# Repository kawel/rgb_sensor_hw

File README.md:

# rgb_sensor_hw
RGB sensor Kicad project

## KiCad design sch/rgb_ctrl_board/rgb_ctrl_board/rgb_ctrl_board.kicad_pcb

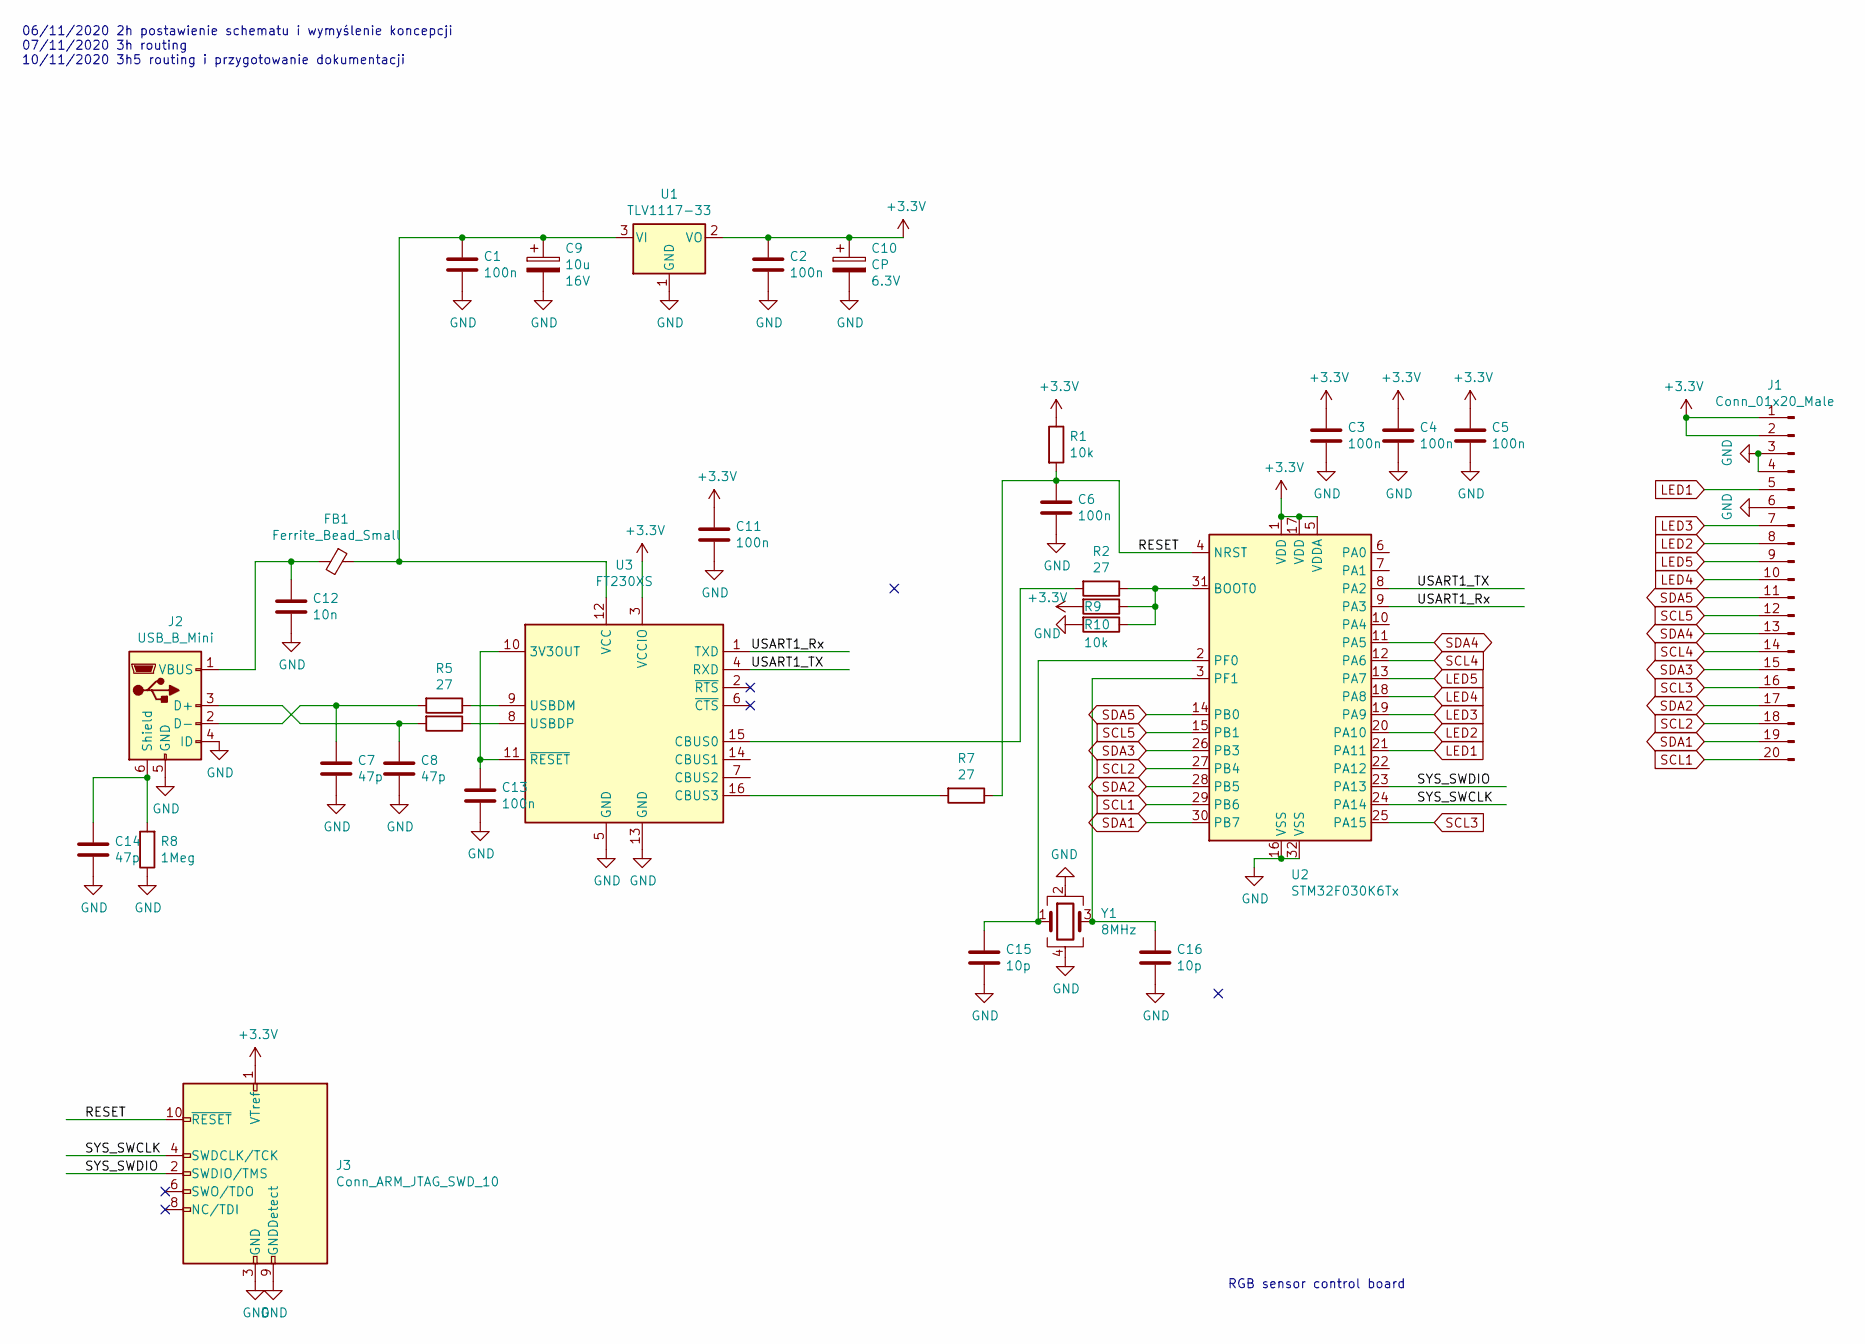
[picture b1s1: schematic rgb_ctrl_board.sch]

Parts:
C1, C2, C3, C4, C5, C6, C11, C13: 100n; C_0603_1608Metric_Pad1.08x0.95mm_HandSolder
C7, C8, C14: 47p; C_0603_1608Metric_Pad1.08x0.95mm_HandSolder
C9: 10u; C_Elec_4x5.4; Voltage 16V
C10: CP; C_Elec_5x5.4; Voltage 6.3V
C12: 10n; C_0603_1608Metric_Pad1.08x0.95mm_HandSolder
C15, C16: 10p; C_0603_1608Metric_Pad1.08x0.95mm_HandSolder
FB1: Ferrite_Bead_Small; L_0603_1608Metric_Pad1.05x0.95mm_HandSolder
J1: Conn_01x20_Male; JST_PHD_S20B-PHDSS_2x10_P2.00mm_Horizontal
J2: USB_B_Mini; USB_Micro-B_Molex_47346-0001
J3: Conn_ARM_JTAG_SWD_10; PinHeader_2x05_P1.27mm_Vertical
R1, R9, R10: 10k; R_0603_1608Metric_Pad0.98x0.95mm_HandSolder
R2, R5, R6, R7: 27; R_0603_1608Metric_Pad0.98x0.95mm_HandSolder
R8: 1Meg; R_0603_1608Metric_Pad0.98x0.95mm_HandSolder
U1: TLV1117-33; SOT-223-3_TabPin2
U2: STM32F030K6Tx; LQFP-32_7x7mm_P0.8mm
U3: FT230XS; SSOP-16_3.9x4.9mm_P0.635mm
Y1: 8MHz; Oscillator_SMD_TXC_7C-4Pin_5.0x3.2mm_HandSoldering

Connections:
+3V3: C2.1, C3.1, C4.1, C5.1, C10.1, C11.1, J1.1, J1.2, J3.1 (VTref), R1.1, R9.2, U1.2 (VO), U2.1 (VDD), U2.5 (VDDA), U2.17 (VDD), U3.3 (VCCIO)
/RESET: C6.1, J3.10 (~RESET~), R1.2, R7.1, U2.4 (NRST)
/SYS_SWCLK: J3.4 (SWDCLK/TCK), U2.24 (PA14)
/SYS_SWDIO: J3.2 (SWDIO/TMS), U2.23 (PA13)
/USART1_Rx: U2.9 (PA3), U3.1 (TXD)
/USART1_TX: U2.8 (PA2), U3.4 (RXD)
GND: C1.2, C2.2, C3.2, C4.2, C5.2, C6.2, C7.2, C8.2, C9.2, C10.2, C11.2, C12.2, C13.2, C14.2, C15.2, C16.2, J1.3, J1.4, J1.6, J2.4 (ID), J2.5 (GND), J3.3 (GND), J3.5 (GND), J3.9 (GNDDetect), R8.1, R10.2, U1.1 (GND), U2.16 (VSS), U2.32 (VSS), U3.5 (GND), U3.13 (GND), Y1.2, Y1.4
LED1: J1.5, U2.21 (PA11)
LED2: J1.8, U2.20 (PA10)
LED3: J1.7, U2.19 (PA9)
LED4: J1.10, U2.18 (PA8)
LED5: J1.9, U2.13 (PA7)
unnamed: C1.1, C9.1, FB1.1, U1.3 (VI), U3.12 (VCC)
unnamed: C7.1, J2.2 (D-), R5.2
unnamed: C8.1, J2.3 (D+), R6.2
unnamed: C12.1, FB1.2, J2.1 (VBUS)
unnamed: C13.1, U3.10 (3V3OUT), U3.11 (~RESET)
unnamed: C14.1, J2.6 (Shield), R8.2
unnamed: C15.1, U2.2 (PF0), Y1.1
unnamed: C16.1, U2.3 (PF1), Y1.3
unnamed: R2.2, U3.15 (CBUS0)
unnamed: R5.1, U3.9 (USBDM)
unnamed: R6.1, U3.8 (USBDP)
unnamed: R7.2, U3.16 (CBUS3)
unnamed: R2.1, R9.1, R10.1, U2.31 (BOOT0)
SCL1: J1.20, U2.29 (PB6)
SCL2: J1.18, U2.27 (PB4)
SCL3: J1.16, U2.25 (PA15)
SCL4: J1.14, U2.12 (PA6)
SCL5: J1.12, U2.15 (PB1)
SDA1: J1.19, U2.30 (PB7)
SDA2: J1.17, U2.28 (PB5)
SDA3: J1.15, U2.26 (PB3)
SDA4: J1.13, U2.11 (PA5)
SDA5: J1.11, U2.14 (PB0)

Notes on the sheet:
06/11/2020 2h postawienie schematu i wymyślenie koncepcji 07/11/2020 3h routing 10/11/2020 3h5 routing i przygotowanie dokumentacji
RGB sensor control board

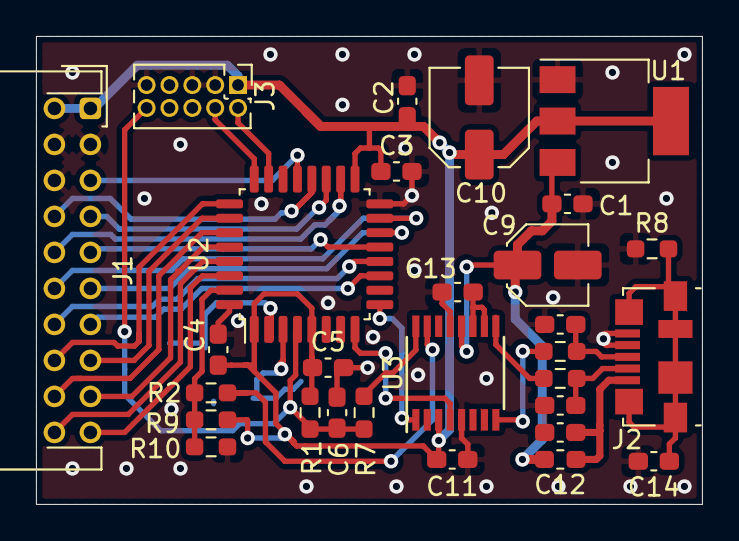
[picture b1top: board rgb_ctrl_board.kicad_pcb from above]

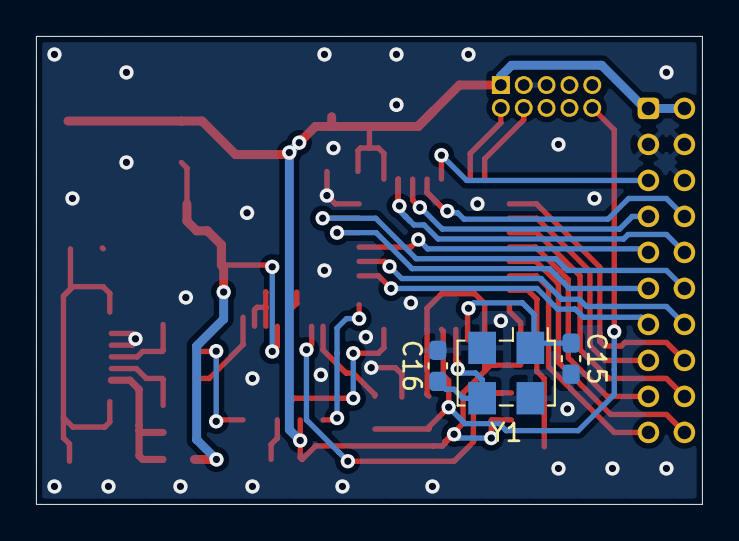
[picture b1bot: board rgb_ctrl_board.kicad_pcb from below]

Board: 2 copper layers, 37.0 x 26.0 mm, 32 parts (3 on the bottom side), 35 nets.

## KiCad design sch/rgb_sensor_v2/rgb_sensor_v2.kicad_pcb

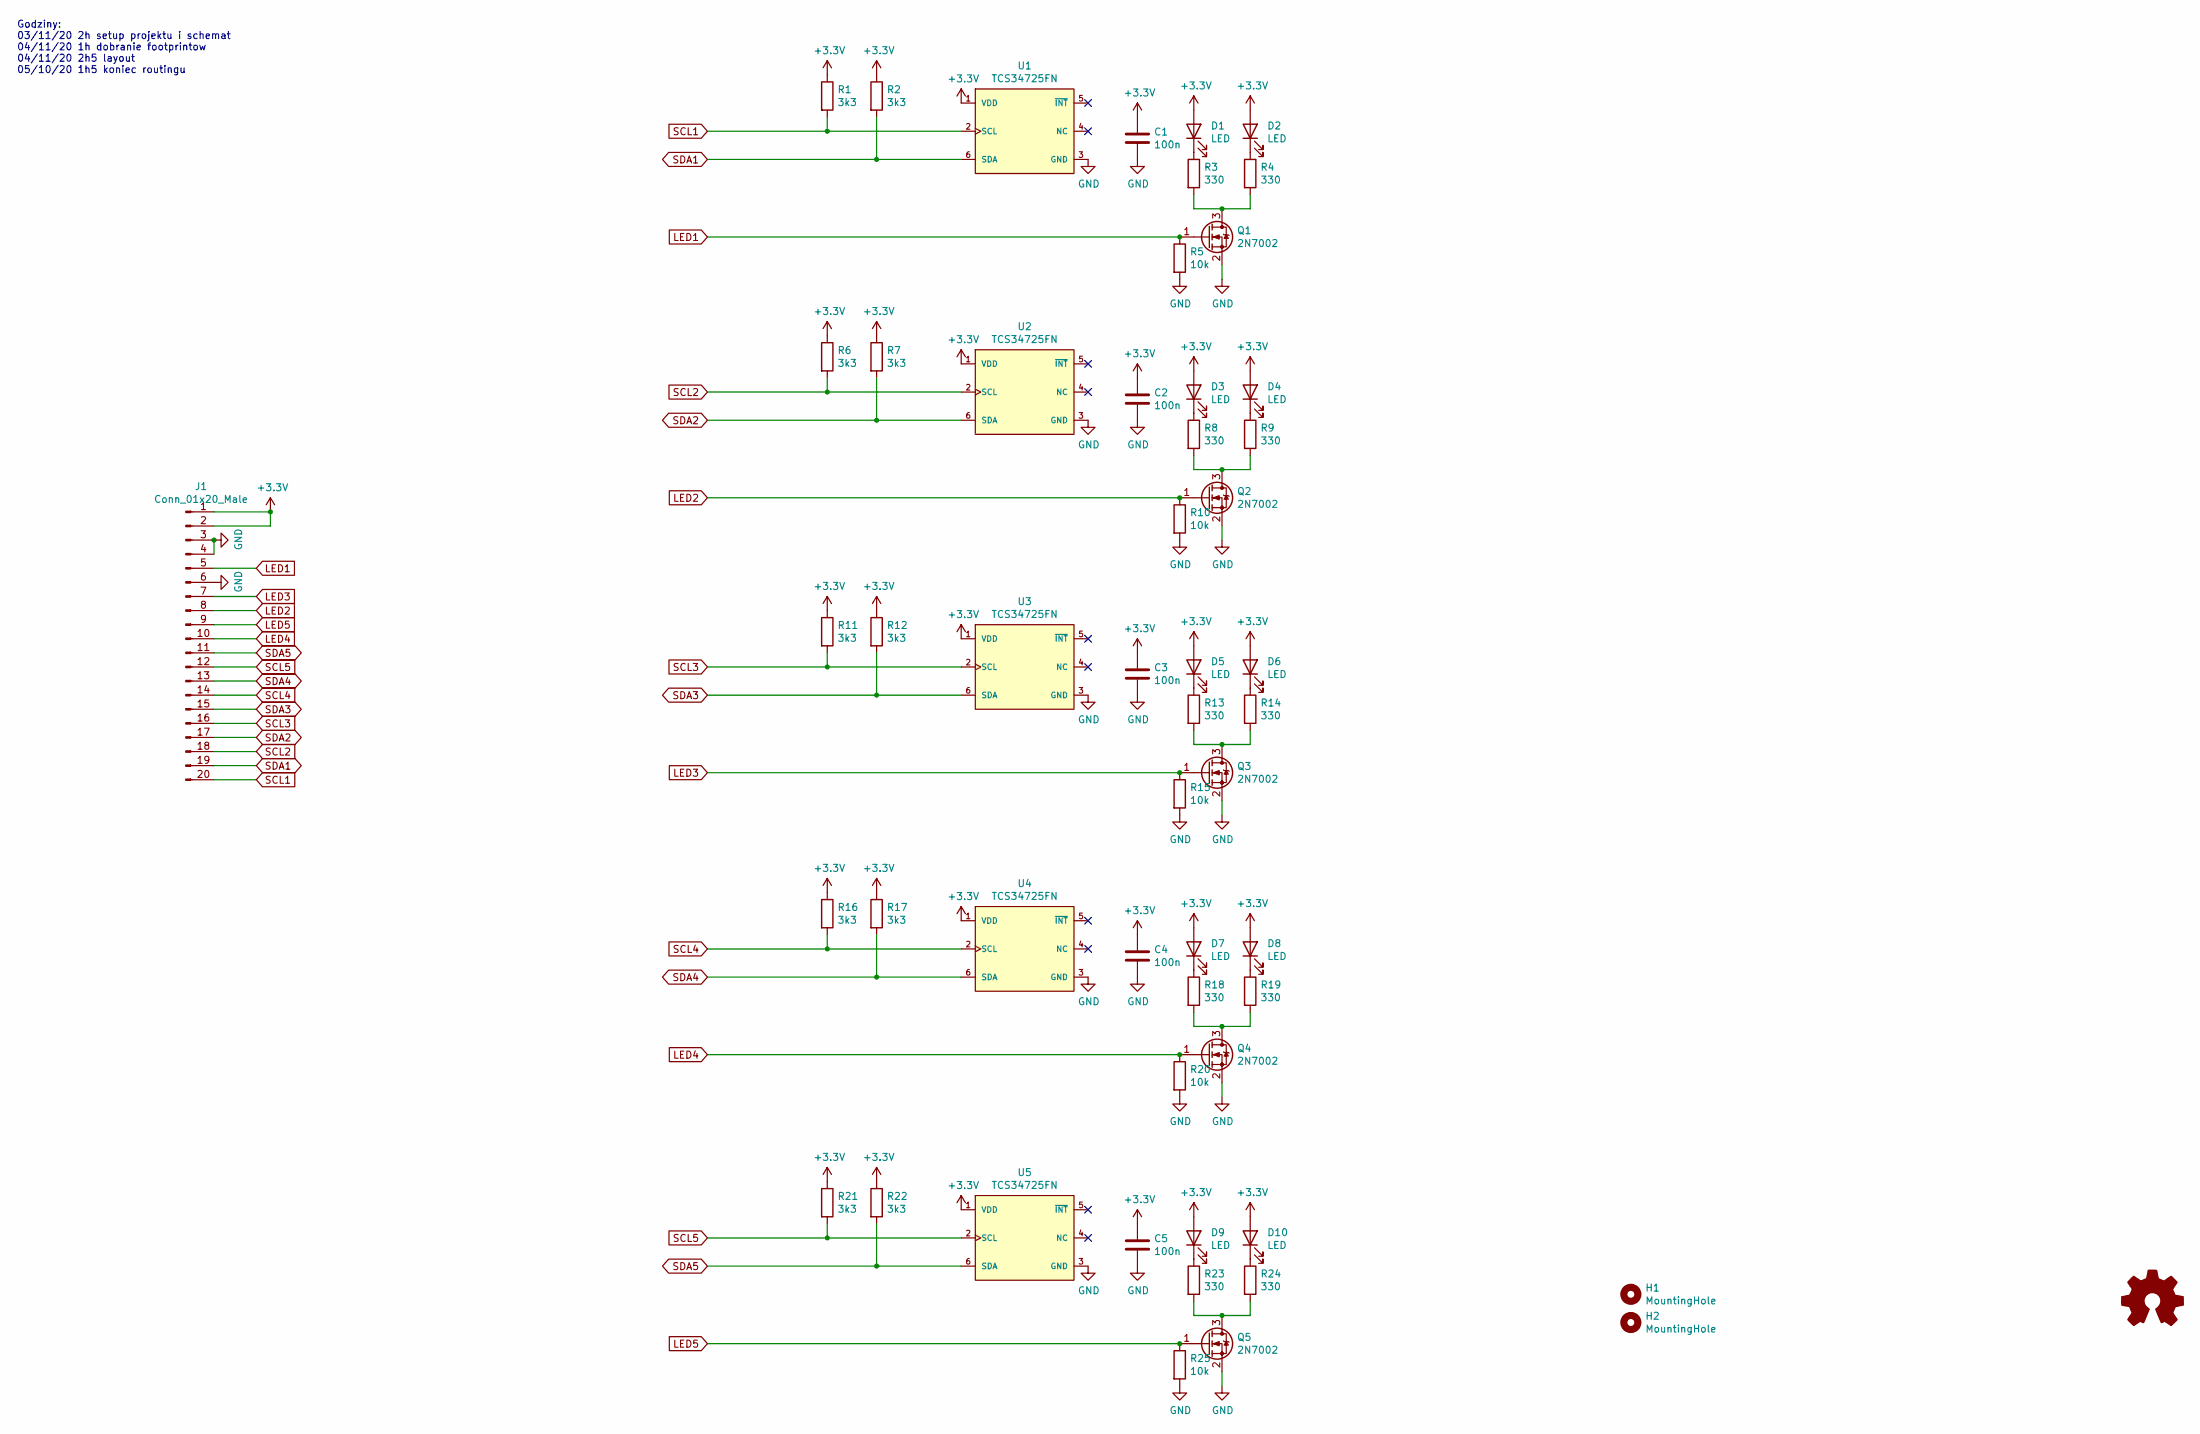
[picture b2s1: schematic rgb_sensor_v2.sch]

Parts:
C1, C2, C3, C4, C5: 100n; C_0603_1608Metric_Pad1.08x0.95mm_HandSolder
D1, D2, D3, D4, D5, D6, D7, D8, D9, D10: LED; D_0603_1608Metric_Castellated
H1, H2: MountingHole; MountingHole_2.2mm_M2_DIN965_Pad
J1: Conn_01x20_Male; JST_PHD_S20B-PHDSS_2x10_P2.00mm_Horizontal
Q1, Q2, Q3, Q4, Q5: 2N7002; SOT-23
R1, R2, R6, R7, R11, R12, R16, R17, R21, R22: 3k3; R_0603_1608Metric_Pad0.98x0.95mm_HandSolder
R3, R4, R8, R9, R13, R14, R18, R19, R23, R24: 330; R_0603_1608Metric_Pad0.98x0.95mm_HandSolder
R5, R10, R15, R20, R25: 10k; R_0603_1608Metric_Pad0.98x0.95mm_HandSolder
U1, U2, U3, U4, U5: TCS34725FN; AMS-TCS34725FN-MFG; mouser part number 985-TCS34725FN; digikey description IC COLOR CONV LIGHT-DGTL 6-DFN

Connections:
+3V3: C1.1, C2.1, C3.1, C4.1, C5.1, D1.2 (A), D2.2 (A), D3.2 (A), D4.2 (A), D5.2 (A), D6.2 (A), D7.2 (A), D8.2 (A), D9.2 (A), D10.2 (A), J1.1, J1.2, R1.1, R2.1, R6.1, R7.1, R11.1, R12.1, R16.1, R17.1, R21.1, R22.1, U1.1 (VDD), U2.1 (VDD), U3.1 (VDD), U4.1 (VDD), U5.1 (VDD)
GND: C1.2, C2.2, C3.2, C4.2, C5.2, J1.3, J1.4, J1.6, Q1.2 (S), Q2.2 (S), Q3.2 (S), Q4.2 (S), Q5.2 (S), R5.2, R10.2, R15.2, R20.2, R25.2, U1.3 (GND), U2.3 (GND), U3.3 (GND), U4.3 (GND), U5.3 (GND)
LED1: J1.5, Q1.1 (G), R5.1
LED2: J1.8, Q2.1 (G), R10.1
LED3: J1.7, Q3.1 (G), R15.1
LED4: J1.10, Q4.1 (G), R20.1
LED5: J1.9, Q5.1 (G), R25.1
unnamed: D1.1 (K), R3.1
unnamed: D2.1 (K), R4.1
unnamed: D3.1 (K), R8.1
unnamed: D4.1 (K), R9.1
unnamed: D5.1 (K), R13.1
unnamed: D6.1 (K), R14.1
unnamed: D7.1 (K), R18.1
unnamed: D8.1 (K), R19.1
unnamed: D9.1 (K), R23.1
unnamed: D10.1 (K), R24.1
unnamed: Q1.3 (D), R3.2, R4.2
unnamed: Q2.3 (D), R8.2, R9.2
unnamed: Q3.3 (D), R13.2, R14.2
unnamed: Q4.3 (D), R18.2, R19.2
unnamed: Q5.3 (D), R23.2, R24.2
SCL1: J1.20, R1.2, U1.2 (SCL)
SCL2: J1.18, R6.2, U2.2 (SCL)
SCL3: J1.16, R11.2, U3.2 (SCL)
SCL4: J1.14, R16.2, U4.2 (SCL)
SCL5: J1.12, R21.2, U5.2 (SCL)
SDA1: J1.19, R2.2, U1.6 (SDA)
SDA2: J1.17, R7.2, U2.6 (SDA)
SDA3: J1.15, R12.2, U3.6 (SDA)
SDA4: J1.13, R17.2, U4.6 (SDA)
SDA5: J1.11, R22.2, U5.6 (SDA)

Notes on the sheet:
Godziny: 03/11/20 2h setup projektu i schemat 04/11/20 1h dobranie footprintow 04/11/20 2h5 layout 05/10/20 1h5 koniec routingu

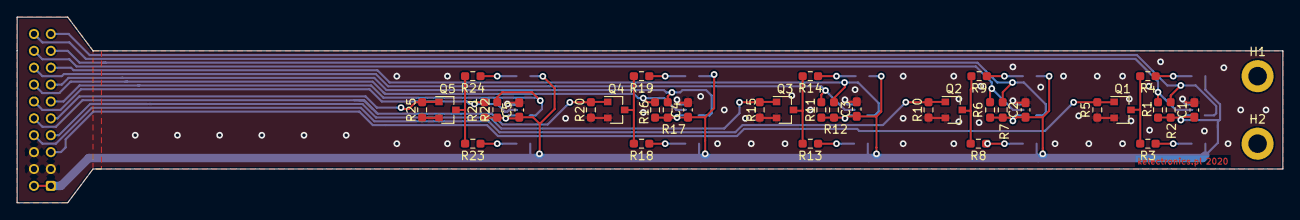
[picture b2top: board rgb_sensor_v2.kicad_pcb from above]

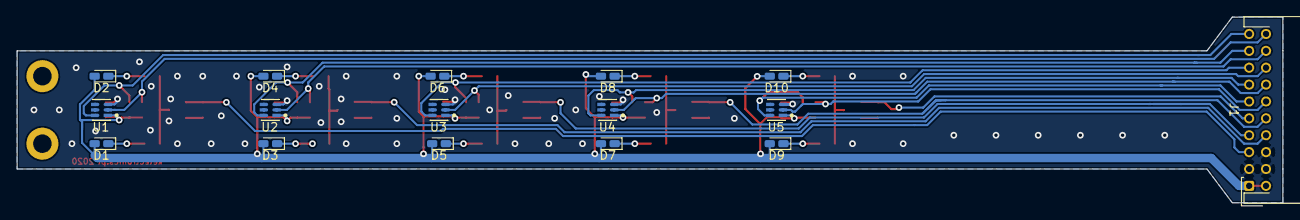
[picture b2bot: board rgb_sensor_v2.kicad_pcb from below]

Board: 2 copper layers, 150.0 x 22.0 mm, 53 parts (16 on the bottom side), 32 nets.

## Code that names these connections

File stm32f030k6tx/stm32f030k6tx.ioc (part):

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Mcu.Name=STM32F030K6Tx
Mcu.Package=LQFP32
Mcu.UserName=STM32F030K6Tx
PA10.Signal=S_TIM1_CH3
PA11.Signal=S_TIM1_CH4
PA13.Mode=Serial_Wire
PA13.Signal=SYS_SWDIO
PA14.Mode=Serial_Wire
PA14.Signal=SYS_SWCLK
PA15.Signal=GPIO_Output
PA2.Mode=Asynchronous
PA2.Signal=USART1_TX
PA3.Mode=Asynchronous
PA3.Signal=USART1_RX
PA5.Signal=GPIO_Output
PA6.Signal=GPIO_Input
PA7.Signal=S_TIM3_CH2
PA8.Signal=S_TIM1_CH1
PA9.Signal=S_TIM1_CH2
PB0.Signal=GPIO_Output
PB1.Signal=GPIO_Input
PB3.Signal=GPIO_Input
PB4.Signal=GPIO_Output
PB5.Signal=GPIO_Input
PB6.Signal=GPIO_Input
PB7.Signal=GPIO_Output
board=custom

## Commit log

2020-11-04 init commit
    Schematics ready
2020-11-04 some layout done
    beefore changing pin assignment on main connector
2020-11-04 zrobiony routing ścieżek
2020-11-05 Zapisany postęp godzinowy
2020-11-05 Pullus routed
2020-11-06 add fab outputs but those are not gerber
2020-11-09 daodana konfiguracja cube
2020-11-09 dodana plytka ctrl i zrobiony routing w 90%
2020-11-10 skończony routing ctrl
2020-11-10 drobne poprawki
2020-11-16 add gerber files
2020-11-17 Add boms
    1h30m
2021-03-05 add mechanics
